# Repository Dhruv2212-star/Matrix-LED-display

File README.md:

# What is it? 
A simple 8x8 LED arrangment that uses MAX7219 LED driver to controll each LED individualy and uses RP2040 to store the code and  
send the data to Driver to create the image
# How to use it?
write a code in C++ and flash it onto the RP2040 to create the paterns onto the LED matrix 

**Images**

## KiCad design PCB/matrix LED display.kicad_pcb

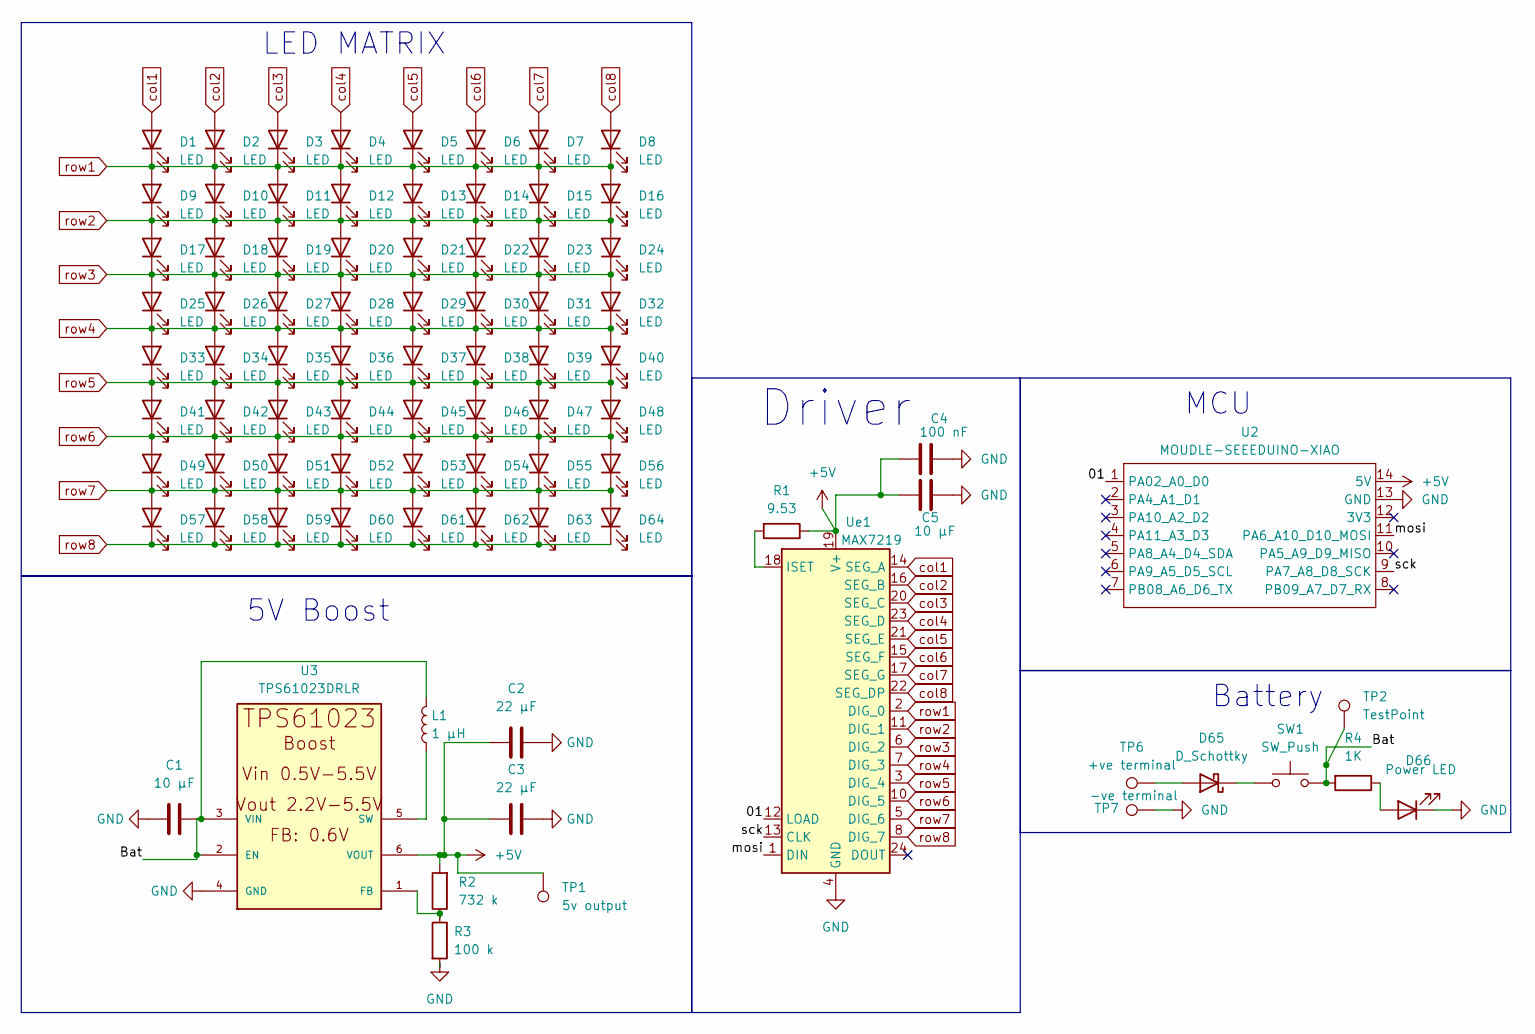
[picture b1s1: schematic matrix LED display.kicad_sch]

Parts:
C1, C5: 10 µF; C_0805_2012Metric
C2, C3: 22 µF; C_0805_2012Metric
C4: 100 nF; C_0805_2012Metric
D1, D2, D3, D4, D5, D6, D7, D8, D9, D10, D11, D12, D13, D14, D15, D16, D17, D18, D19, D20, D21, D22, D23, D24, D25, D26, D27, D28, D29, D30, D31, D32, D33, D34, D35, D36, D37, D38, D39, D40, D41, D42, D43, D44, D45, D46, D47, D48, D49, D50, D51, D52, D53, D54, D55, D56, D57, D58, D59, D60, D61, D62, D63, D64: LED; LED_Everlight-SMD3528_3.5x2.8mm_67-21ST
D65: D_Schottky; D_SMA
D66: Power LED; LED_0201_0603Metric_Pad0.64x0.40mm_HandSolder
L1: 1 µH; L_Sunlord_SWPA8040S
R1: 9.53; R_0805_2012Metric_Pad1.20x1.40mm_HandSolder
R2: 732 k; R_0805_2012Metric_Pad1.20x1.40mm_HandSolder
R3: 100 k; R_0805_2012Metric_Pad1.20x1.40mm_HandSolder
R4: 1K; R_0805_2012Metric_Pad1.20x1.40mm_HandSolder
SW1: SW_Push; SW_SPST_TL3342
TP1: 5v output; TestPoint_Pad_D1.0mm
TP2: TestPoint; TestPoint_Pad_D1.0mm
TP6: +ve terminal; SolderWirePad_1x01_SMD_2x4mm
TP7: -ve terminal; SolderWirePad_1x01_SMD_2x4mm
U2: MOUDLE-SEEEDUINO-XIAO; XIAO-Generic-Hybrid-14P-2.54-21X17.8MM
U3: TPS61023DRLR; SOT563-ORI
Ue1: MAX7219; SOIC-24W_7.5x15.4mm_P1.27mm

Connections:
+5V: C2.1, C3.1, C4.1, C5.1, R1.1, R2.2, TP1.1 (1_1), U2.14 (5V), U3.6 (VOUT), Ue1.19 (V+)
/01: U2.1 (PA02_A0_D0), Ue1.12 (LOAD)
/Bat: C1.1, L1.2, R4.2, SW1.2, TP2.1 (1_1), U3.2 (EN), U3.3 (VIN)
/mosi: U2.11 (PA6_A10_D10_MOSI), Ue1.1 (DIN)
/sck: U2.9 (PA7_A8_D8_SCK), Ue1.13 (CLK)
GND: C1.2, C2.2, C3.2, C4.2, C5.2, D66.1 (K), R3.2, TP7.1 (1_1), U2.13 (GND), U3.4 (GND), Ue1.4 (GND), Ue1.9 (GND)
unnamed: D65.2 (A), TP6.1 (1_1)
unnamed: D65.1 (K), SW1.1
unnamed: D66.2 (A), R4.1
unnamed: R2.1, R3.1, U3.1 (FB)
unnamed: L1.1, U3.5 (SW)
unnamed: R1.2, Ue1.18 (ISET)
col1: D1.2 (A), Ue1.14 (SEG_A)
col2: D2.2 (A), Ue1.16 (SEG_B)
col3: D3.2 (A), Ue1.20 (SEG_C)
col4: D4.2 (A), Ue1.23 (SEG_D)
col5: D5.2 (A), Ue1.21 (SEG_E)
col6: D6.2 (A), Ue1.15 (SEG_F)
col7: D7.2 (A), Ue1.17 (SEG_G)
col8: D8.2 (A), Ue1.22 (SEG_DP)
row1: D1.1 (K), D2.1 (K), D3.1 (K), D4.1 (K), D5.1 (K), D6.1 (K), D7.1 (K), D8.1 (K), D9.2 (A), D10.2 (A), D11.2 (A), D12.2 (A), D13.2 (A), D14.2 (A), D15.2 (A), D16.2 (A), Ue1.2 (DIG_0)
row2: D9.1 (K), D10.1 (K), D11.1 (K), D12.1 (K), D13.1 (K), D14.1 (K), D15.1 (K), D16.1 (K), D17.2 (A), D18.2 (A), D19.2 (A), D20.2 (A), D21.2 (A), D22.2 (A), D23.2 (A), D24.2 (A), Ue1.11 (DIG_1)
row3: D17.1 (K), D18.1 (K), D19.1 (K), D20.1 (K), D21.1 (K), D22.1 (K), D23.1 (K), D24.1 (K), D25.2 (A), D26.2 (A), D27.2 (A), D28.2 (A), D29.2 (A), D30.2 (A), D31.2 (A), D32.2 (A), Ue1.6 (DIG_2)
row4: D25.1 (K), D26.1 (K), D27.1 (K), D28.1 (K), D29.1 (K), D30.1 (K), D31.1 (K), D32.1 (K), D33.2 (A), D34.2 (A), D35.2 (A), D36.2 (A), D37.2 (A), D38.2 (A), D39.2 (A), D40.2 (A), Ue1.7 (DIG_3)
row5: D33.1 (K), D34.1 (K), D35.1 (K), D36.1 (K), D37.1 (K), D38.1 (K), D39.1 (K), D40.1 (K), D41.2 (A), D42.2 (A), D43.2 (A), D44.2 (A), D45.2 (A), D46.2 (A), D47.2 (A), D48.2 (A), Ue1.3 (DIG_4)
row6: D41.1 (K), D42.1 (K), D43.1 (K), D44.1 (K), D45.1 (K), D46.1 (K), D47.1 (K), D48.1 (K), D49.2 (A), D50.2 (A), D51.2 (A), D52.2 (A), D53.2 (A), D54.2 (A), D55.2 (A), D56.2 (A), Ue1.10 (DIG_5)
row7: D49.1 (K), D50.1 (K), D51.1 (K), D52.1 (K), D53.1 (K), D54.1 (K), D55.1 (K), D56.1 (K), D57.2 (A), D58.2 (A), D59.2 (A), D60.2 (A), D61.2 (A), D62.2 (A), D63.2 (A), D64.2 (A), Ue1.5 (DIG_6)
row8: D57.1 (K), D58.1 (K), D59.1 (K), D60.1 (K), D61.1 (K), D62.1 (K), D63.1 (K), D64.1 (K), Ue1.8 (DIG_7)

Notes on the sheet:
5V Boost
LED MATRIX
MCU
Driver
Battery

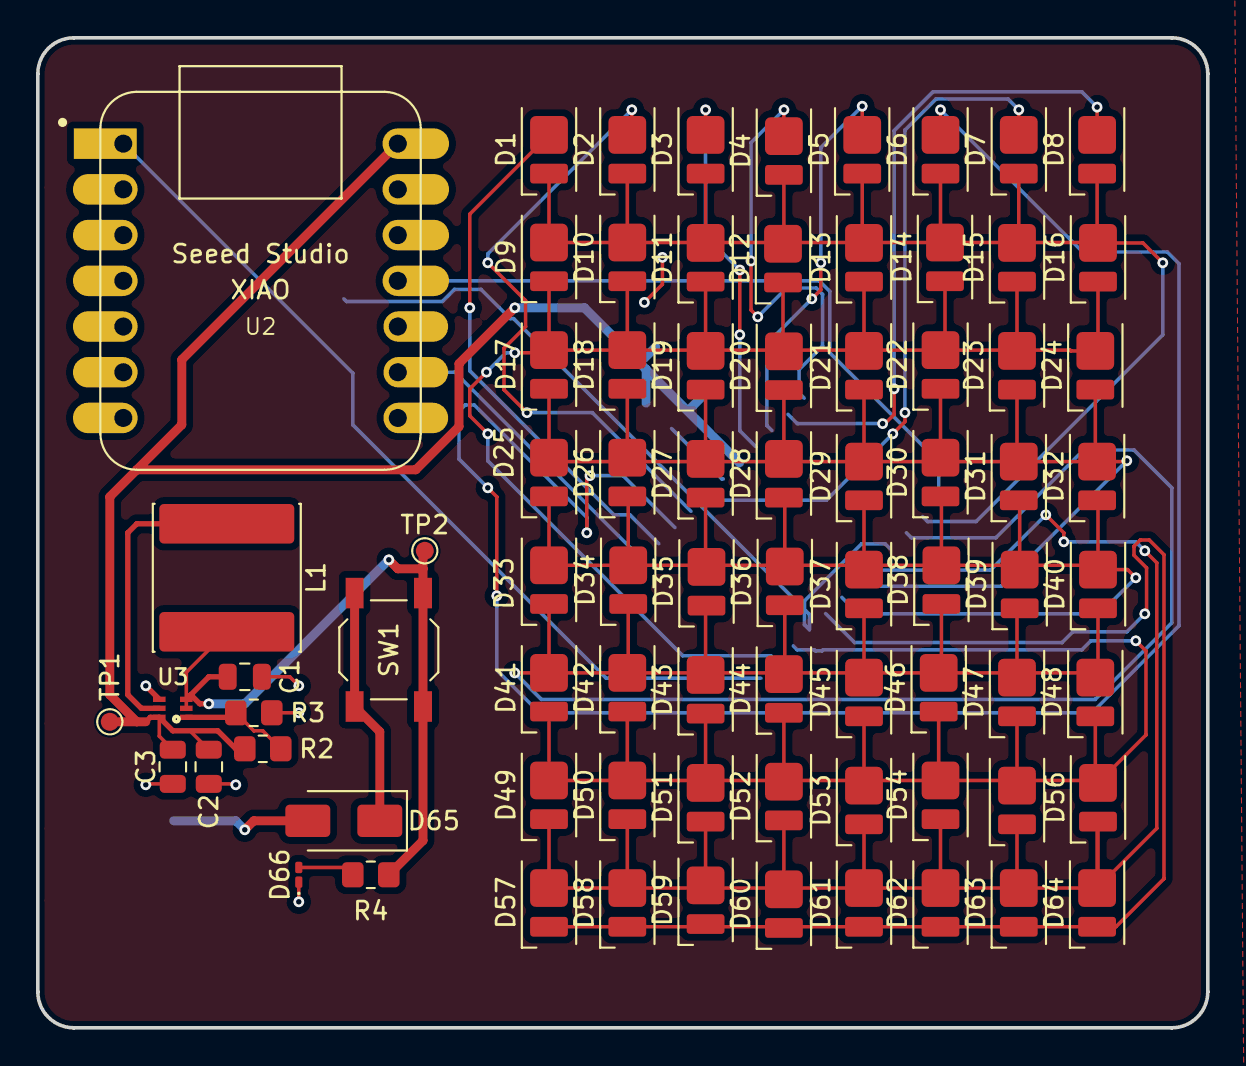
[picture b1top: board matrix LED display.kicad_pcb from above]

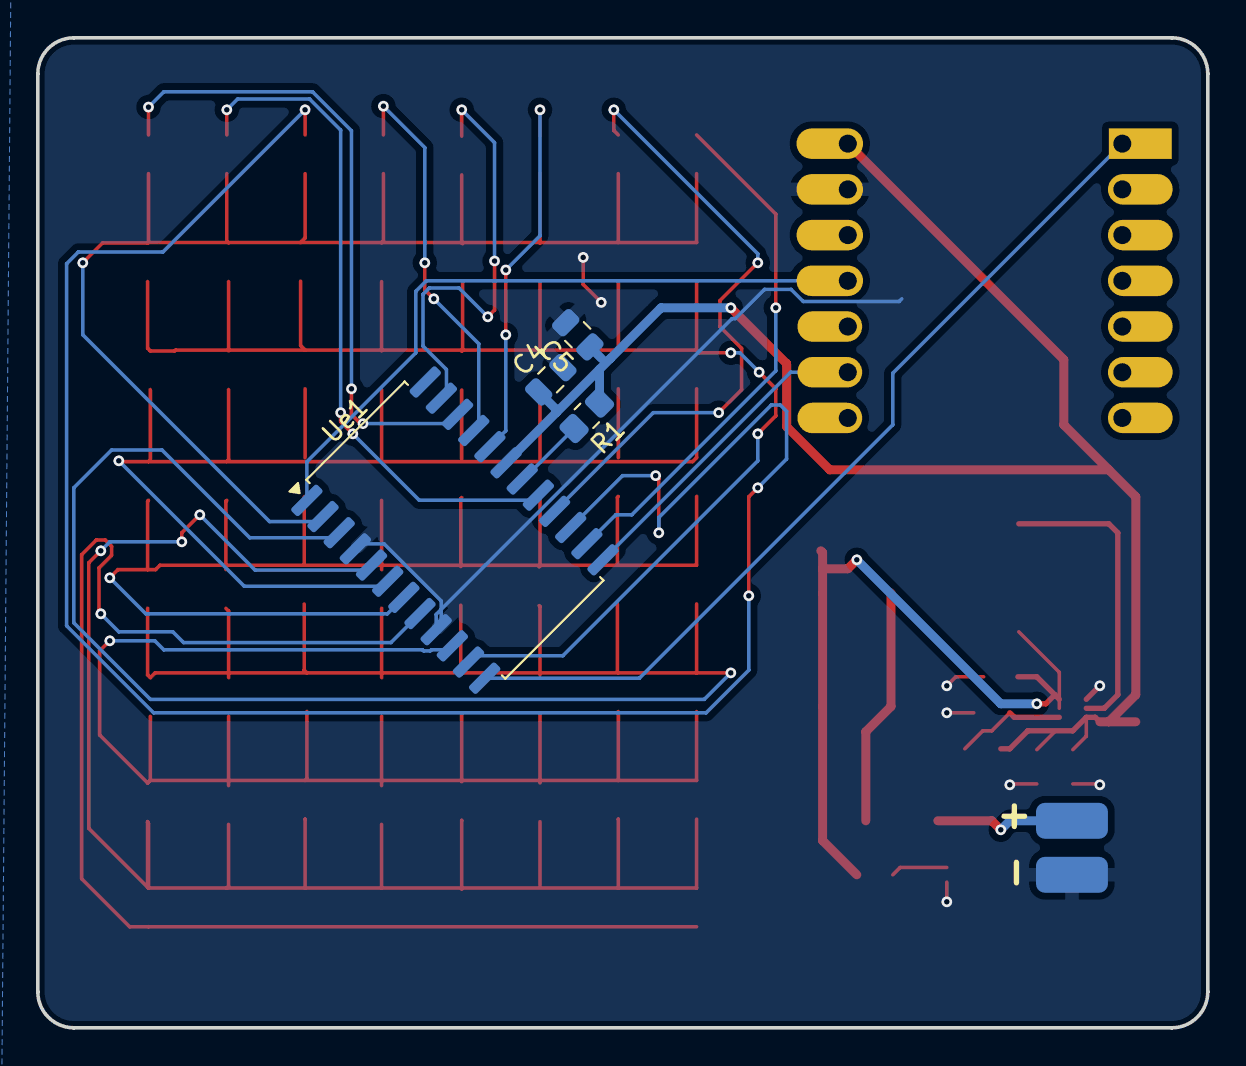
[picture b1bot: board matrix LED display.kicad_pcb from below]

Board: 2 copper layers, 65.0 x 55.0 mm, 84 parts (6 on the bottom side), 28 nets.
